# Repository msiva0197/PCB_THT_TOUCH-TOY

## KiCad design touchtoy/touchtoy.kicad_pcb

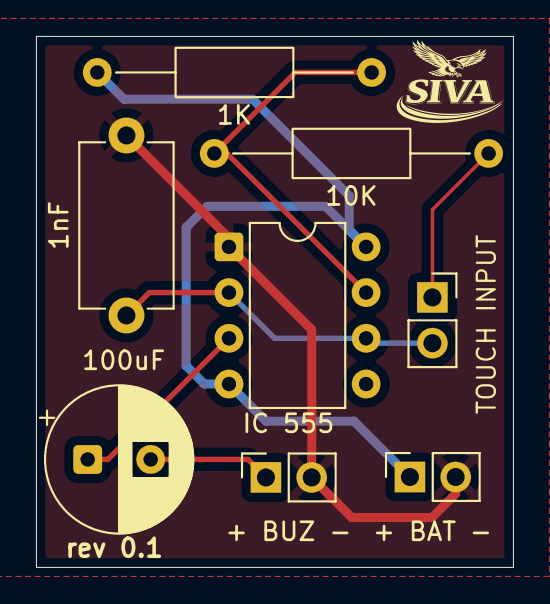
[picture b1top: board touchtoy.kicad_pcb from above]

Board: 2 copper layers, 26.5 x 29.5 mm, 8 parts (0 on the bottom side), 7 nets.

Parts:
1K: 1k; R_Axial_DIN0207_L6.3mm_D2.5mm_P15.24mm_Horizontal
1nF: 1nF; C_Disc_D9.0mm_W5.0mm_P10.00mm
10K: 10k; R_Axial_DIN0207_L6.3mm_D2.5mm_P15.24mm_Horizontal
100uF: 100uF; CP_Radial_D8.0mm_P3.50mm
+ BAT -: battery; PinSocket_1x02_P2.54mm_Vertical
+ BUZ -: buzzer out; PinSocket_1x02_P2.54mm_Vertical
IC 555: NE555P; DIP-8_W7.62mm
TOUCH INPUT: touch input; PinSocket_1x02_P2.54mm_Vertical

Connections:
/DIS: 1K.1, 10K.2, IC 555.7 (DISCH)
/TR: 1nF.1, IC 555.2 (TRIG), IC 555.6 (THRES), TOUCH INPUT.2
/out: 100uF.1, IC 555.3 (OUT)
GND: 1nF.2, + BAT -.2, + BUZ -.2, IC 555.1 (GND)
unnamed: 100uF.2, + BUZ -.1
unnamed: 10K.1, TOUCH INPUT.1
VCC: 1K.2, + BAT -.1, IC 555.4 (~RST), IC 555.8 (VCC)

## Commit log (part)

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2026-06-09 Add Touch Toy THT version design files
